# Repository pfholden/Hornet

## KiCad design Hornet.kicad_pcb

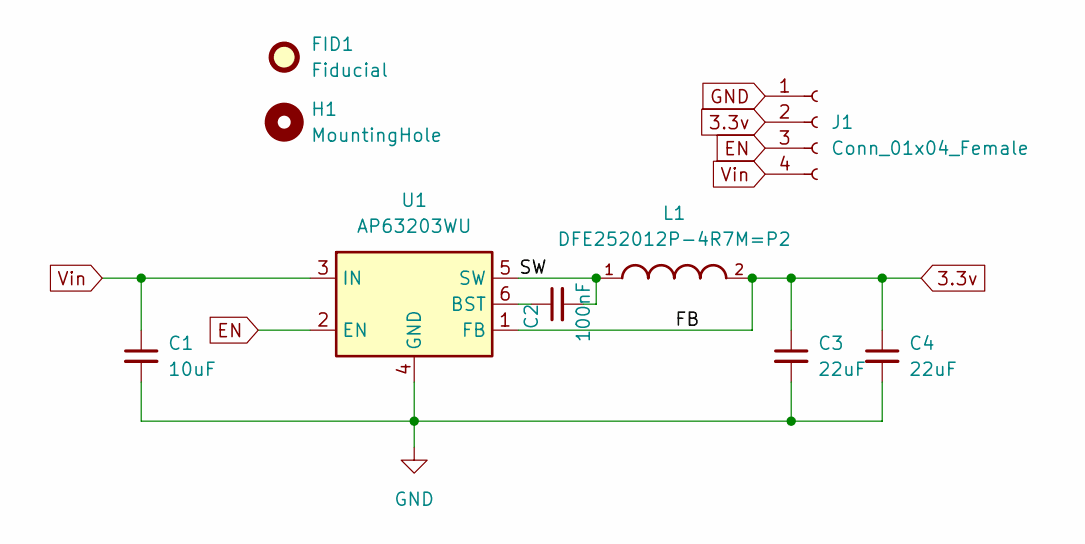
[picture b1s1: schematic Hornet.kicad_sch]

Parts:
C1: 10uF; C_0805_2012Metric
C2: 100nF; C_0603_1608Metric
C3, C4: 22uF; C_0603_1608Metric
FID1: Fiducial; Fiducial_0.5mm_Mask1.5mm
H1: MountingHole; MountingHole_3.2mm_M3_ISO7380
J1: Conn_01x04_Female; PinHeader_1x04_P2.54mm_Vertical
L1: DFE252012P-4R7M=P2; INDC2520X120N
U1: AP63203WU; TSOT-23-6

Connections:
3.3v: C3.1, C4.1, J1.2, L1.2, U1.1 (FB)
/SW: C2.2, L1.1, U1.5 (SW)
EN: J1.3, U1.2 (EN)
GND: C1.2, C3.2, C4.2, J1.1, U1.4 (GND)
unnamed: C2.1, U1.6 (BST)
Vin: C1.1, J1.4, U1.3 (IN)

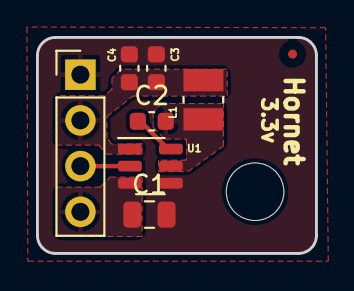
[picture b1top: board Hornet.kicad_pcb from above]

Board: 2 copper layers, 15.5 x 12.0 mm, 9 parts (0 on the bottom side), 6 nets.

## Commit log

2023-06-12 First layout
2023-06-12 Second layout to make board smaller
2023-06-15 New layout and added component part numbers
